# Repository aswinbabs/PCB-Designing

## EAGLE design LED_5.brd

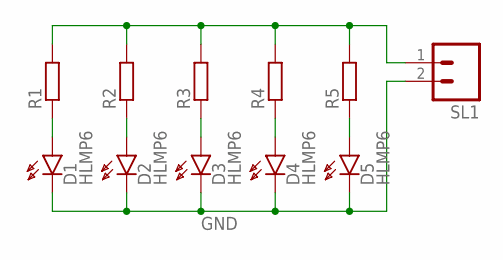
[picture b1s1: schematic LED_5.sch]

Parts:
D1, D2, D3, D4, D5: HLMP6
R1, R2, R3, R4, R5: R-EU_0204/7; 0204/7
SL1: M02; 02P

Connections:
GND: D1.K, D2.K, D3.K, D4.K, D5.K, SL1.2
unnamed: D3.A, D4.A, D5.A, R1.2, R2.2, R3.1, R3.2, R4.1, R4.2, R5.1, R5.2, SL1.1
unnamed: D1.A, R1.1
unnamed: D2.A, R2.1

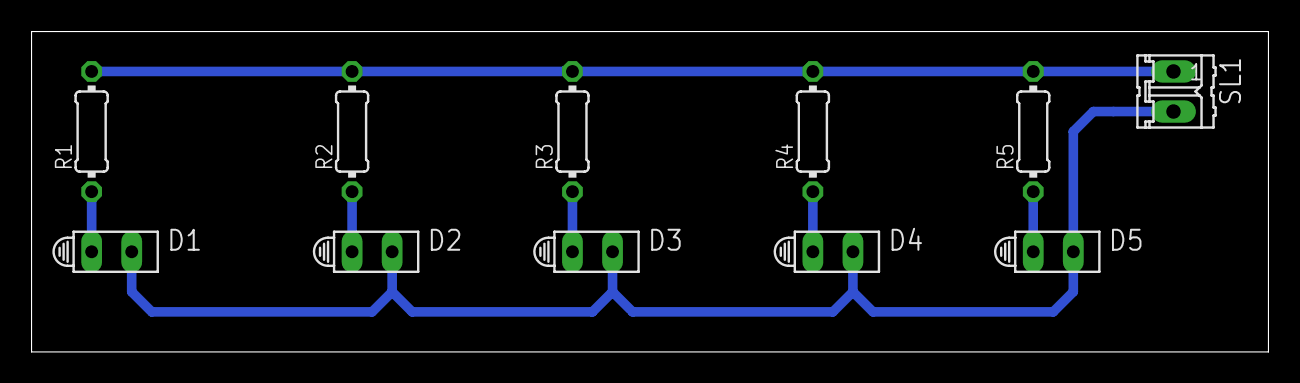
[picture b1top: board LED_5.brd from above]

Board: 2 copper layers, 78.4 x 20.3 mm, 11 parts (0 on the bottom side), 4 nets.

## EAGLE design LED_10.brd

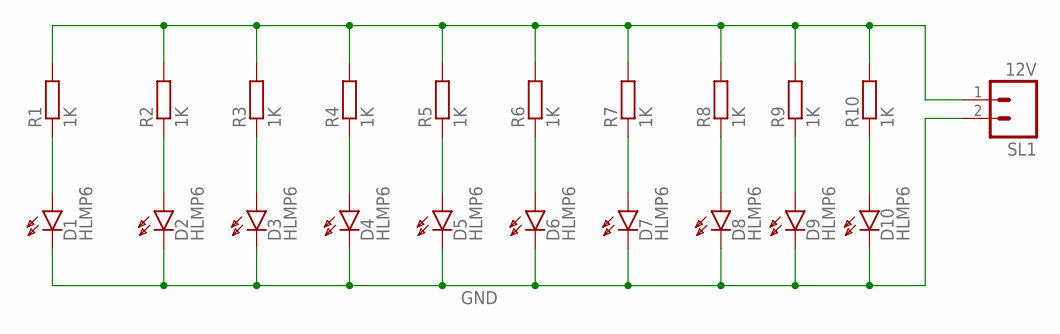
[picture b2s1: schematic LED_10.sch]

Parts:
D1, D2, D3, D4, D5, D6, D7, D8, D9, D10: HLMP6
R1, R2, R3, R4, R5, R6, R7, R8, R9, R10: 1K; 0204/7
SL1: 12V; 02P

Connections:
GND: D1.K, D2.K, D3.K, D4.K, D5.K, D6.K, D7.K, D8.K, D9.K, D10.K, SL1.2
unnamed: D1.A, R1.1
unnamed: D2.A, R2.1
unnamed: R1.2, R2.2, R3.2, R4.2, R5.2, R6.2, R7.2, R8.2, R9.2, R10.2, SL1.1
unnamed: D3.A, R3.1
unnamed: D4.A, R4.1
unnamed: D5.A, R5.1
unnamed: D6.A, R6.1
unnamed: D7.A, R7.1
unnamed: D8.A, R8.1
unnamed: D9.A, R9.1
unnamed: D10.A, R10.1

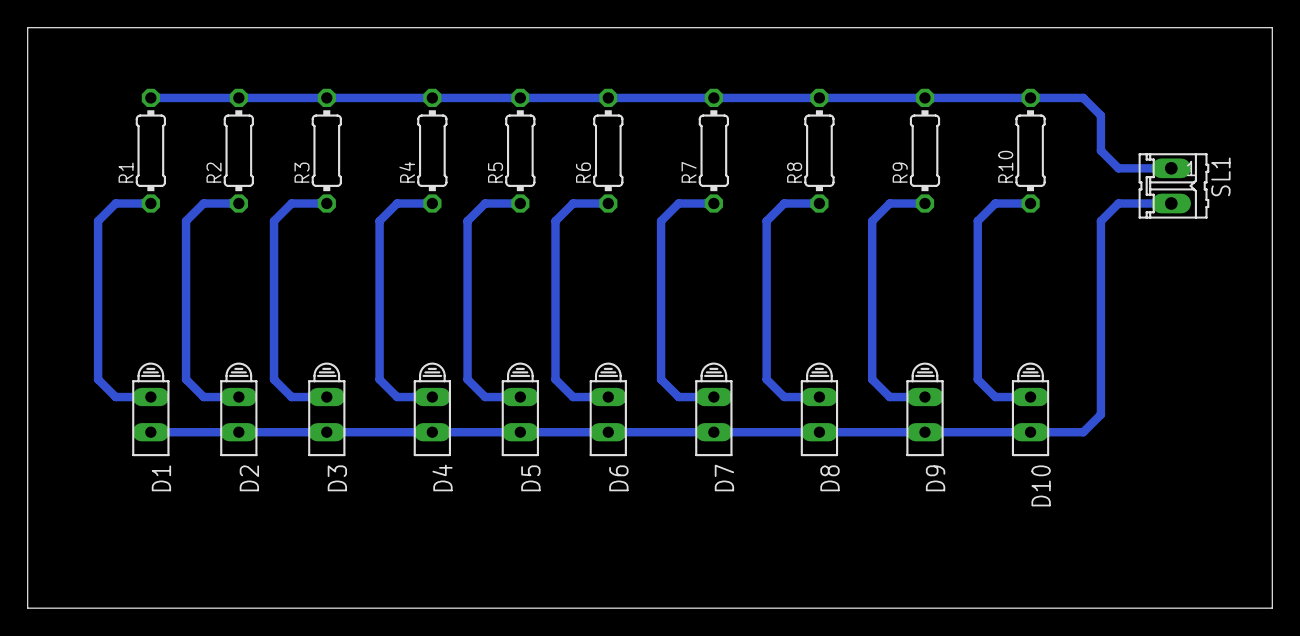
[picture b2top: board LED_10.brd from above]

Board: 2 copper layers, 89.8 x 41.9 mm, 21 parts (0 on the bottom side), 12 nets.
